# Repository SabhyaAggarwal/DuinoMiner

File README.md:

# DuinoMiner
This is a PCB made by me that is used for mining DuinoCoin, a type of cryptocurrency with not too much value. You can mine it with normal small consumer-available chips as well...

## Hardware
### Schematic

### PCB Design

### 3D render

## BOM
|Name                  |Description                                                                                         |Quantity|Total Cost|Link                                                                                                         |Distributor     |
|----------------------|----------------------------------------------------------------------------------------------------|--------|----------|-------------------------------------------------------------------------------------------------------------|----------------|
|PCB                   |Main PCB(cost includes payment fees)                                                                |1       |$1.36     |https://aivon.com/                                                                                           |AIVON           |
|Wemos D1 Mini         |Main chip for Network connection(cost includes tax)                                                 |1       |$2.17     |https://quartzcomponents.com/products/wemos-d1-mini-esp8266-nodemcu-mini-d1-module?variant=39261072392376    |quartz component|
|Pi Pico               |The 3 Picos which actually mine(tax inclusive and shipping grouped with wemos)                      |3       |$12.23    |https://quartzcomponents.com/products/raspberry-pi-pico?variant=37945289801912                               |quartz component|
|0.96 inch oled display|OLED display                                                                                        |1       |$1.71     |https://quartzcomponents.com/collections/all/products/oled-display-0-96-inch-i2c-interface-4-pin-blue-ssd1306|quartz component|
|40 pin male header    |Header pins for the pi picos as they are not included(tax inclusive and shipping grouped with wemos)|3       |$0.26     |https://quartzcomponents.com/products/40-pin-break-away-headers-straight-male-headers?variant=31898065633415 |quartz component|

## Notes

For setup there is a great onboarding setup shown on the OLED screen and you can manage it using the web UI and all. The firmware is taken from https://github.com/JK-Rolling/DuinoI2C_ESP

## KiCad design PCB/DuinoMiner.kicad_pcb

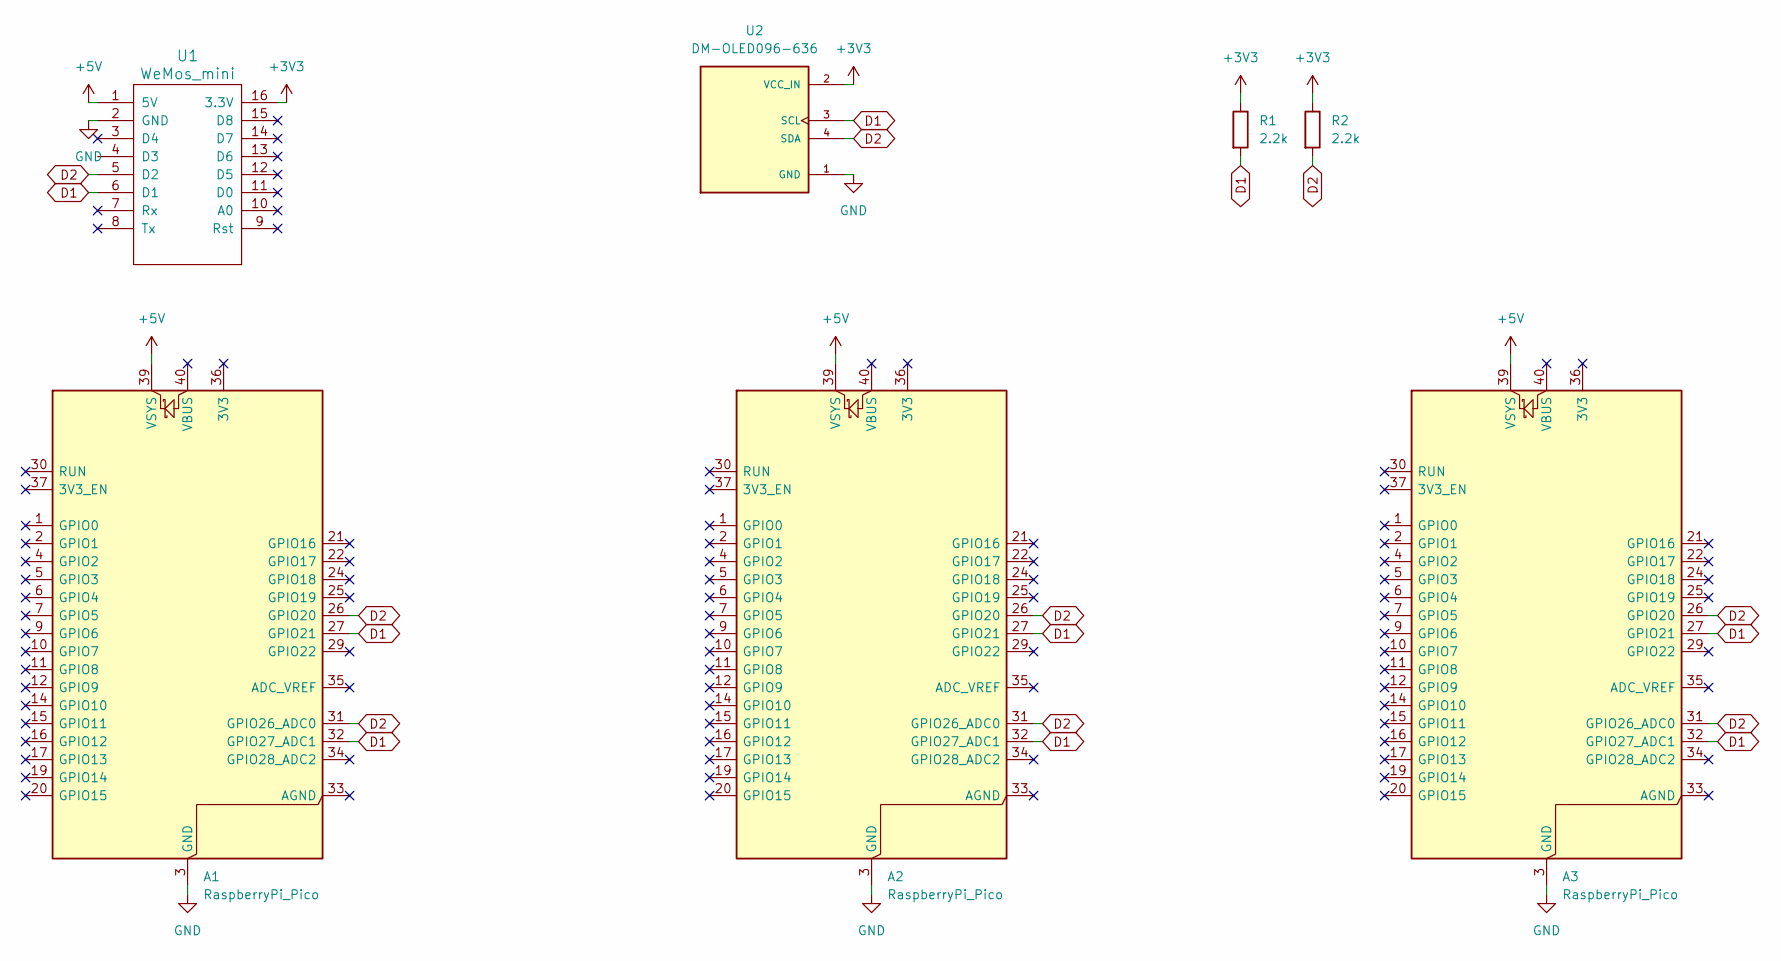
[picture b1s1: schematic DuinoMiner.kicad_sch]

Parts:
A1, A2, A3: RaspberryPi_Pico; RaspberryPi_Pico_Common_THT
R1, R2: 2.2k; R_Axial_DIN0204_L3.6mm_D1.6mm_P7.62mm_Horizontal
U1: WeMos_mini; D1_mini_board
U2: DM-OLED096-636; MODULE_DM-OLED096-636; PARTREV 2018-09-10

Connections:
+3V3: R1.1, R2.1, U1.16 (3.3V), U2.2 (VCC_IN)
+5V: A1.39 (VSYS), A2.39 (VSYS), A3.39 (VSYS), U1.1 (5V)
D1: A1.27 (GPIO21), A1.32 (GPIO27_ADC1), A2.27 (GPIO21), A2.32 (GPIO27_ADC1), A3.27 (GPIO21), A3.32 (GPIO27_ADC1), R1.2, U1.6 (D1), U2.3 (SCL)
D2: A1.26 (GPIO20), A1.31 (GPIO26_ADC0), A2.26 (GPIO20), A2.31 (GPIO26_ADC0), A3.26 (GPIO20), A3.31 (GPIO26_ADC0), R2.2, U1.5 (D2), U2.4 (SDA)
GND: A1.3 (GND), A1.8 (GND), A1.13 (GND), A1.18 (GND), A1.23 (GND), A1.28 (GND), A1.38 (GND), A2.3 (GND), A2.8 (GND), A2.13 (GND), A2.18 (GND), A2.23 (GND), A2.28 (GND), A2.38 (GND), A3.3 (GND), A3.8 (GND), A3.13 (GND), A3.18 (GND), A3.23 (GND), A3.28 (GND), A3.38 (GND), U1.2 (GND), U2.1 (GND)

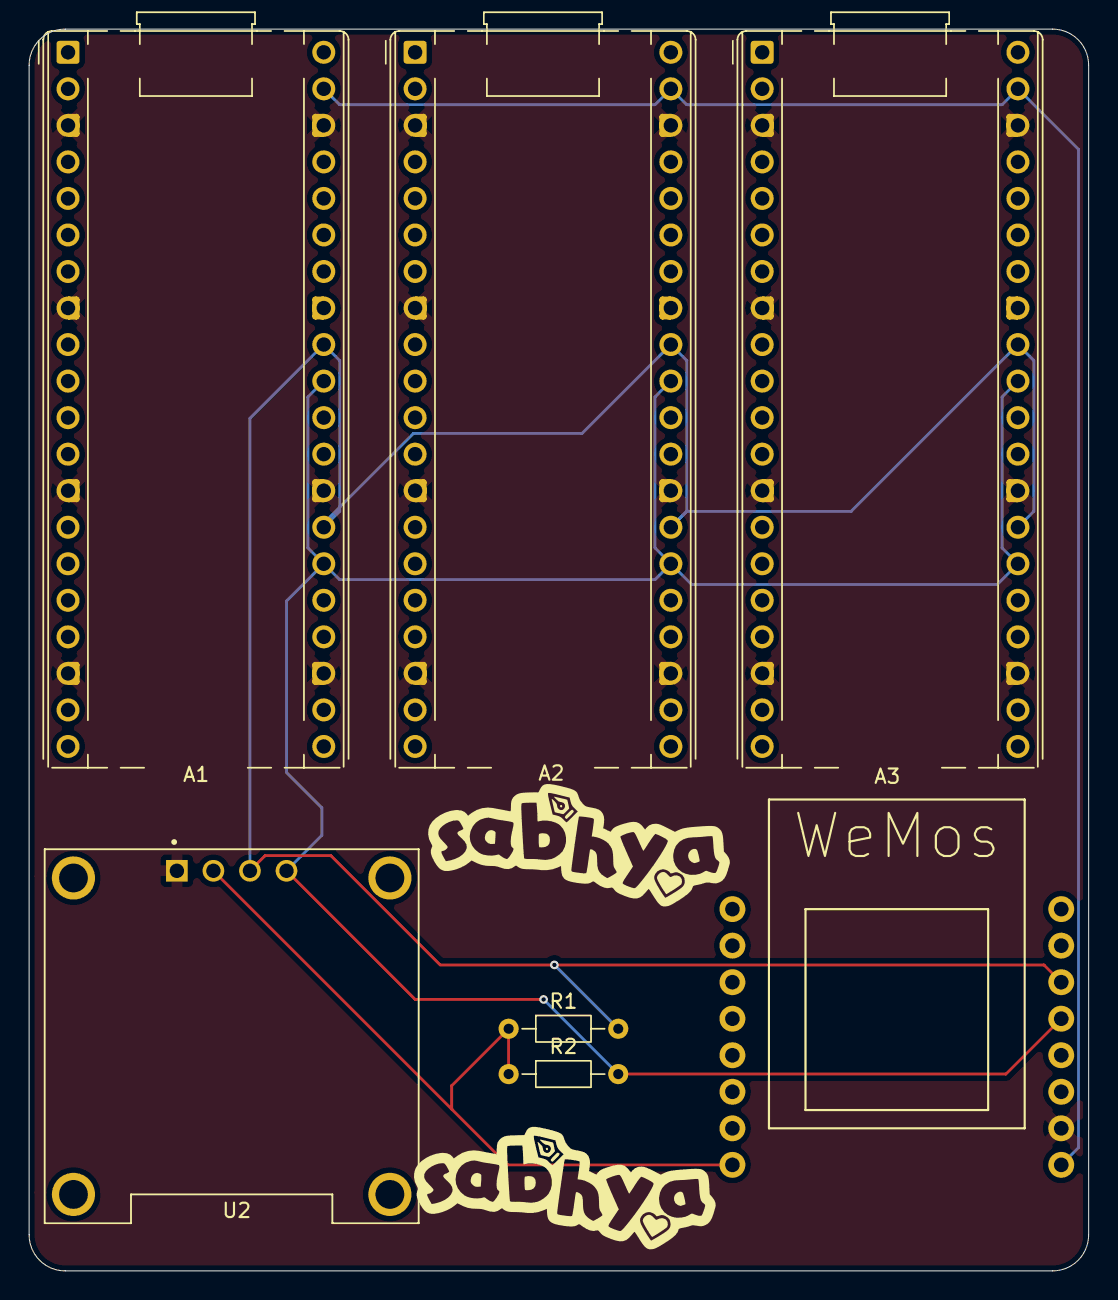
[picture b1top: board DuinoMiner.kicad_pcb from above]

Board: 2 copper layers, 73.7 x 86.3 mm, 7 parts (1 on the bottom side), 5 nets.
